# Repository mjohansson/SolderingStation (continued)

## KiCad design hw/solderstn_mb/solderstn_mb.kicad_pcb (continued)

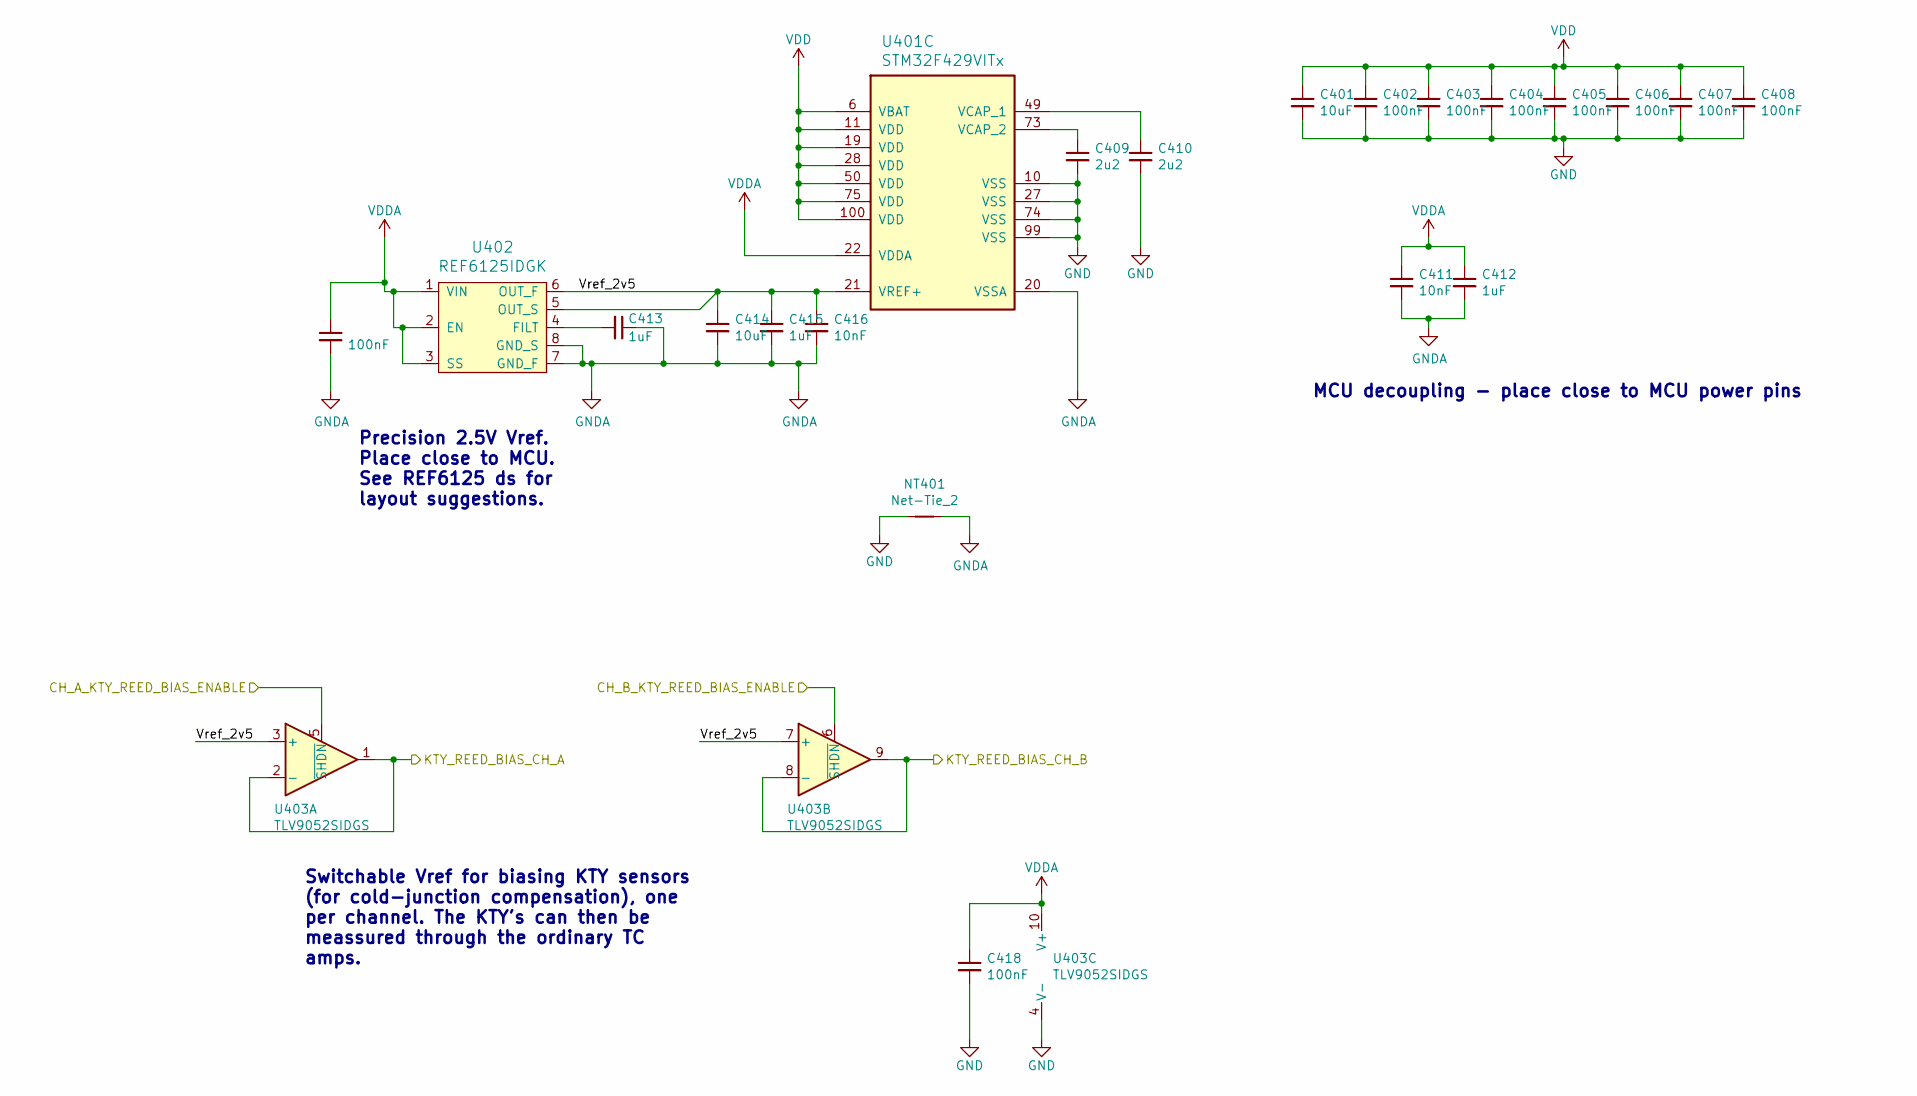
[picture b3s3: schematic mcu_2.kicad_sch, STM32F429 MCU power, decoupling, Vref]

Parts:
C401, C414: 10uF; C_0402_1005Metric; JLC_part Basic
C402, C403, C404, C405, C406, C407, C408, C417, C418: 100nF; C_0402_1005Metric; JLC_part Basic
C409, C410: 2u2; C_0603_1608Metric; JLC_part Basic
C411, C416: 10nF; C_0402_1005Metric; JLC_part Basic
C412, C413, C415: 1uF; C_0402_1005Metric; JLC_part Basic
NT401: Net-Tie_2; NetTie-2_SMD_Pad2.0mm
U401: STM32F429VITx; LQFP-100_14x14mm_P0.5mm; JLC_part Extended
U402: REF6125IDGK; VSSOP-8_3.0x3.0mm_P0.65mm
U403: TLV9052SIDGS; VSSOP-10_3x3mm_P0.5mm

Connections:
/STM32F429 MCU/CH_A_KTY_REED_BIAS_EN: U403.5 (~SHDN); also elsewhere on the board
/STM32F429 MCU/CH_B_KTY_REED_BIAS_EN: U403.6 (~SHDN); also elsewhere on the board
/STM32F429 PWR/KTY_REED_BIAS_CH_A: U403.1, U403.2 (-); also elsewhere on the board
/STM32F429 PWR/KTY_REED_BIAS_CH_B: U403.8 (-), U403.9; also elsewhere on the board
/STM32F429 PWR/Vref_2v5: C414.1, C415.1, C416.1, U401.21 (VREF+), U402.5 (OUT_S), U402.6 (OUT_F), U403.3 (+), U403.7 (+)
AGND: C401.2, C402.2, C403.2, C404.2, C405.2, C406.2, C407.2, C408.2, C409.2, C410.2, C411.2, C412.2, C413.1, C414.2, C415.2, C416.2, C417.2, C418.2, NT401.1, NT401.2, U401.10 (VSS), U401.20 (VSSA), U401.27 (VSS), U401.74 (VSS), U401.99 (VSS), U402.7 (GND_F), U402.8 (GND_S), U403.4 (V-); also elsewhere on the board
AVDD: C411.1, C412.1, C417.1, C418.1, U401.22 (VDDA), U402.1 (VIN), U402.2 (EN), U402.3 (SS), U403.10 (V+); also elsewhere on the board
unnamed: C409.1, U401.73 (VCAP_2)
unnamed: C410.1, U401.49 (VCAP_1)
unnamed: C413.2, U402.4 (FILT)
VCC: C401.1, C402.1, C403.1, C404.1, C405.1, C406.1, C407.1, C408.1, U401.6 (VBAT), U401.11 (VDD), U401.19 (VDD), U401.28 (VDD), U401.50 (VDD), U401.75 (VDD), U401.100 (VDD); also elsewhere on the board

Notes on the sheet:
MCU decoupling - place close to MCU power pins
Precision 2.5V Vref. Place close to MCU. See REF6125 ds for layout suggestions.
Switchable Vref for biasing KTY sensors (for cold-junction compensation), one per channel. The KTY's can then be meassured through the ordinary TC amps.

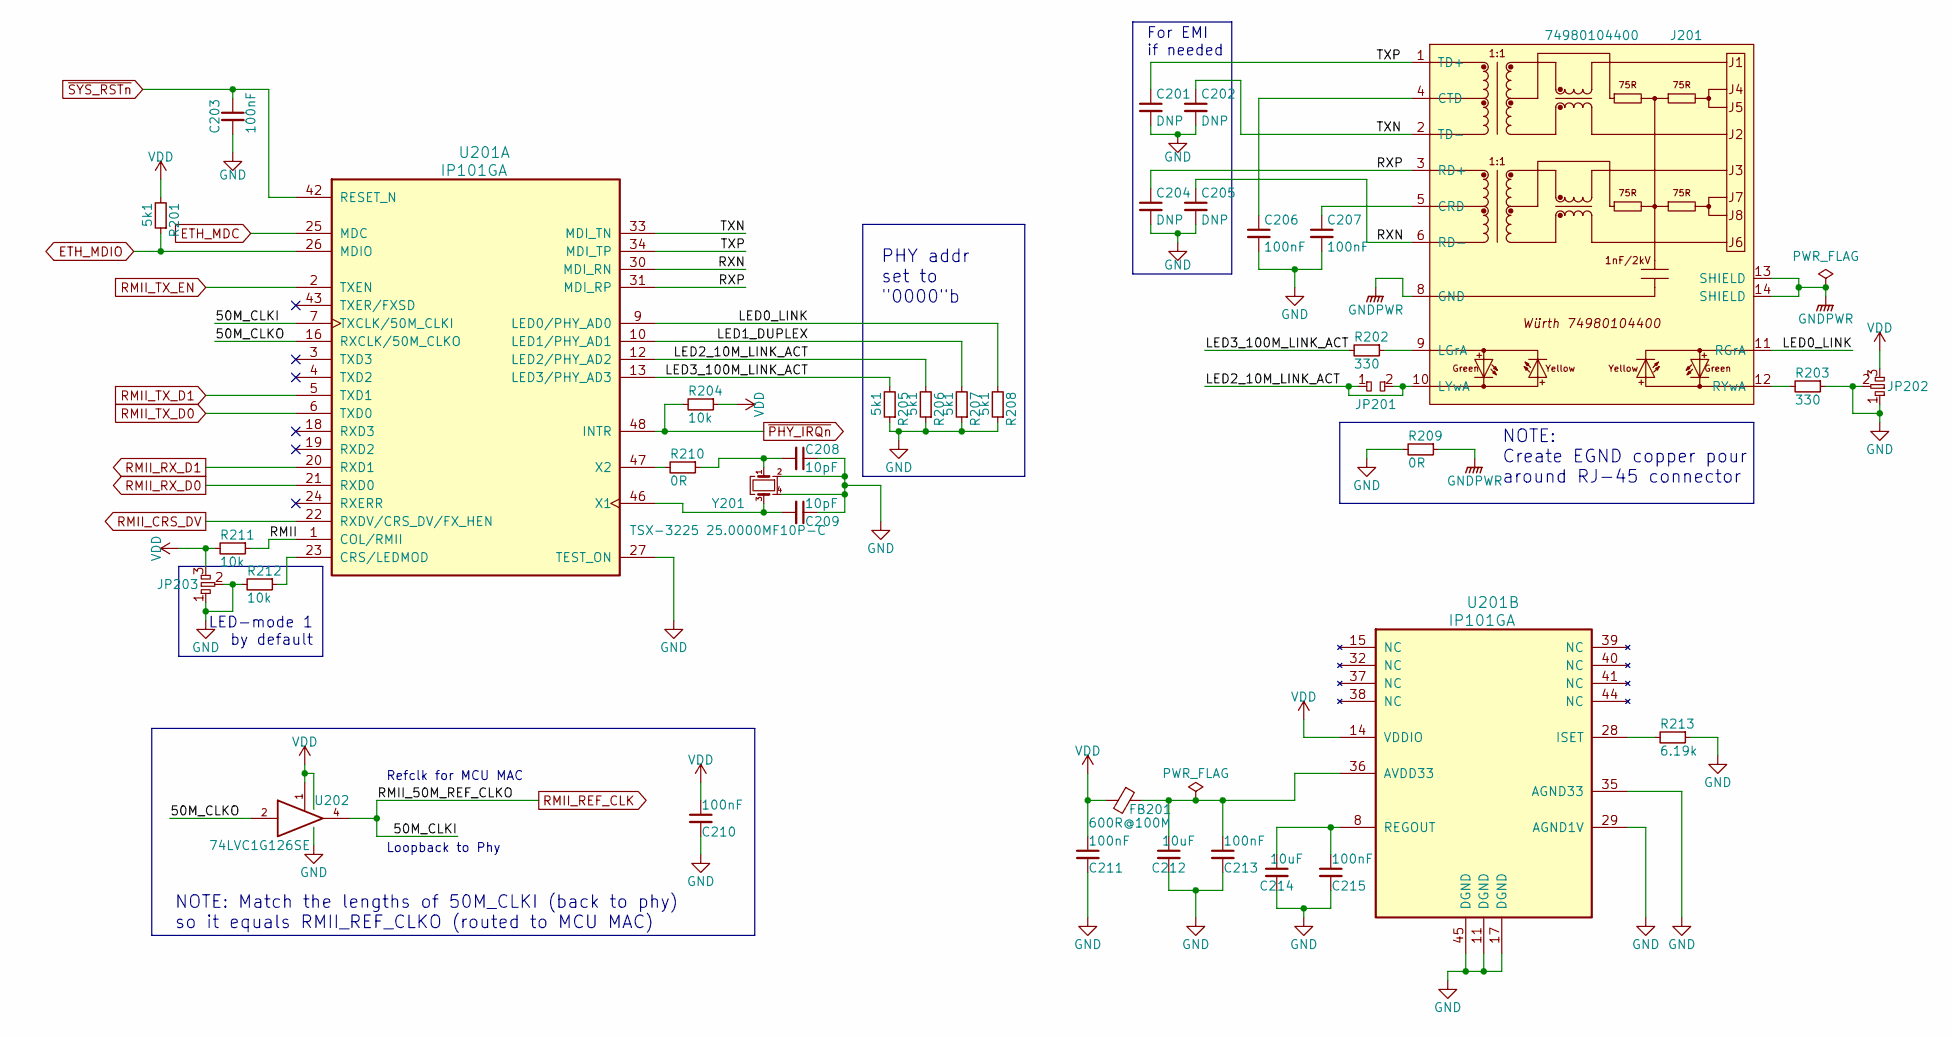
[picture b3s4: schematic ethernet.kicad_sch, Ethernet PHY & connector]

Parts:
C201, C202, C204, C205: DNP; C_0402_1005Metric; JLC_part Basic
C203, C206, C207, C210, C211, C213, C215: 100nF; C_0402_1005Metric; JLC_part Basic
C208, C209: 10pF; C_0402_1005Metric; JLC_part Basic
C212, C214: 10uF; C_0402_1005Metric; JLC_part Basic
FB201: 600R@100M; L_0603_1608Metric; JLC_part Basic
J201: 74980104400; 74980104400_WE-RJ45_LAN_trx
JP201: dogbone_2_ud; db2_ud_0402
JP202, JP203: dogbone_3_ud; db3_ud_0402
R201, R205, R206, R207, R208: 5k1; R_0402_1005Metric; JLC_part Basic
R202, R203: 330; R_0402_1005Metric; JLC_part Basic
R204, R211, R212: 10k; R_0402_1005Metric; JLC_part Basic
R209, R210: 0R; R_0402_1005Metric; JLC_part Basic
R213: 6.19k; R_0402_1005Metric; JLC_part Extended
U201: IP101GA; LQFP-48_7x7mm_P0.5mm; JLC_part Extended
U202: 74LVC1G126SE; SOT-353_SC-70-5_Handsoldering; JLC_part Extended
Y201: TSX-3225 25.0000MF10P-C; Crystal_SMD_SeikoEpson_TSX3225-4Pin_3.2x2.5mm; JLC_part Basic

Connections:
/Ethernet/50M_CLKO: U201.16 (RXCLK/50M_CLKO), U202.2
/Ethernet/LED0_LINK: J201.11 (RGrA), R208.2, U201.9 (LED0/PHY_AD0)
/Ethernet/LED1_DUPLEX: R207.2, U201.10 (LED1/PHY_AD1)
/Ethernet/LED2_10M_LINK_ACT: J201.10 (LYwA), JP201.1, JP201.2, R206.2, U201.12 (LED2/PHY_AD2)
/Ethernet/LED3_100M_LINK_ACT: R202.2, R205.2, U201.13 (LED3/PHY_AD3)
/Ethernet/RMII: R211.1, U201.1 (COL/RMII)
/Ethernet/RXN: C205.1, J201.6 (RD-), U201.30 (MDI_RN)
/Ethernet/RXP: C204.1, J201.3 (RD+), U201.31 (MDI_RP)
/Ethernet/TXN: C202.1, J201.2 (TD-), U201.33 (MDI_TN)
/Ethernet/TXP: C201.1, J201.1 (TD+), U201.34 (MDI_TP)
AGND: C201.2, C202.2, C203.2, C204.2, C205.2, C206.2, C207.2, C208.1, C209.1, C210.2, C211.2, C212.2, C213.2, C214.2, C215.2, JP202.1, JP202.2, JP203.1, JP203.2, R203.1, R205.1, R206.1, R207.1, R208.1, R209.2, R212.2, R213.1, U201.11 (DGND), U201.17 (DGND), U201.27 (TEST_ON), U201.29 (AGND1V), U201.35 (AGND33), U201.45 (DGND), U202.3 (GND), Y201.2, Y201.4; also elsewhere on the board
ETH_MDC: U201.25 (MDC); also elsewhere on the board
ETH_MDIO: R201.1, U201.26 (MDIO); also elsewhere on the board
GNDPWR: J201.8 (GND), J201.13 (SHIELD), J201.14 (SHIELD), R209.1
unnamed: C206.1, J201.4 (CTD)
unnamed: C207.1, J201.5 (CRD)
unnamed: C208.2, R210.1, Y201.1
unnamed: C209.2, U201.46 (X1), Y201.3
unnamed: C212.1, C213.1, FB201.1, U201.36 (AVDD33)
unnamed: C214.1, C215.1, U201.8 (REGOUT)
unnamed: J201.9 (LGrA), R202.1
unnamed: J201.12 (RYwA), R203.2
unnamed: R210.2, U201.47 (X2)
unnamed: R212.1, U201.23 (CRS/LEDMOD)
unnamed: R213.2, U201.28 (ISET)
RMII_CRS_DV: U201.22 (RXDV/CRS_DV/FX_HEN); also elsewhere on the board
RMII_REF_CLK: U201.7 (TXCLK/50M_CLKI), U202.4; also elsewhere on the board
RMII_RX_D0: U201.21 (RXD0); also elsewhere on the board
RMII_RX_D1: U201.20 (RXD1); also elsewhere on the board
RMII_TX_D0: U201.6 (TXD0); also elsewhere on the board
RMII_TX_D1: U201.5 (TXD1); also elsewhere on the board
RMII_TX_EN: U201.2 (TXEN); also elsewhere on the board
VCC: C210.1, C211.1, FB201.2, JP202.3, JP203.3, R201.2, R204.1, R211.2, U201.14 (VDDIO), U202.1, U202.5 (VCC); also elsewhere on the board
~PHY_IRQn: R204.2, U201.48 (INTR); also elsewhere on the board
~SYS_RSTn: C203.1, U201.42 (RESET_N); also elsewhere on the board

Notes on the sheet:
Refclk for MCU MAC
NOTE: Create EGND copper pour around RJ-45 connector
PHY addr set to "0000"b
Loopback to Phy
For EMI if needed
LED-mode 1 by default
NOTE: Match the lengths of 50M_CLKI (back to phy) so it equals RMII_REF_CLKO (routed to MCU MAC)

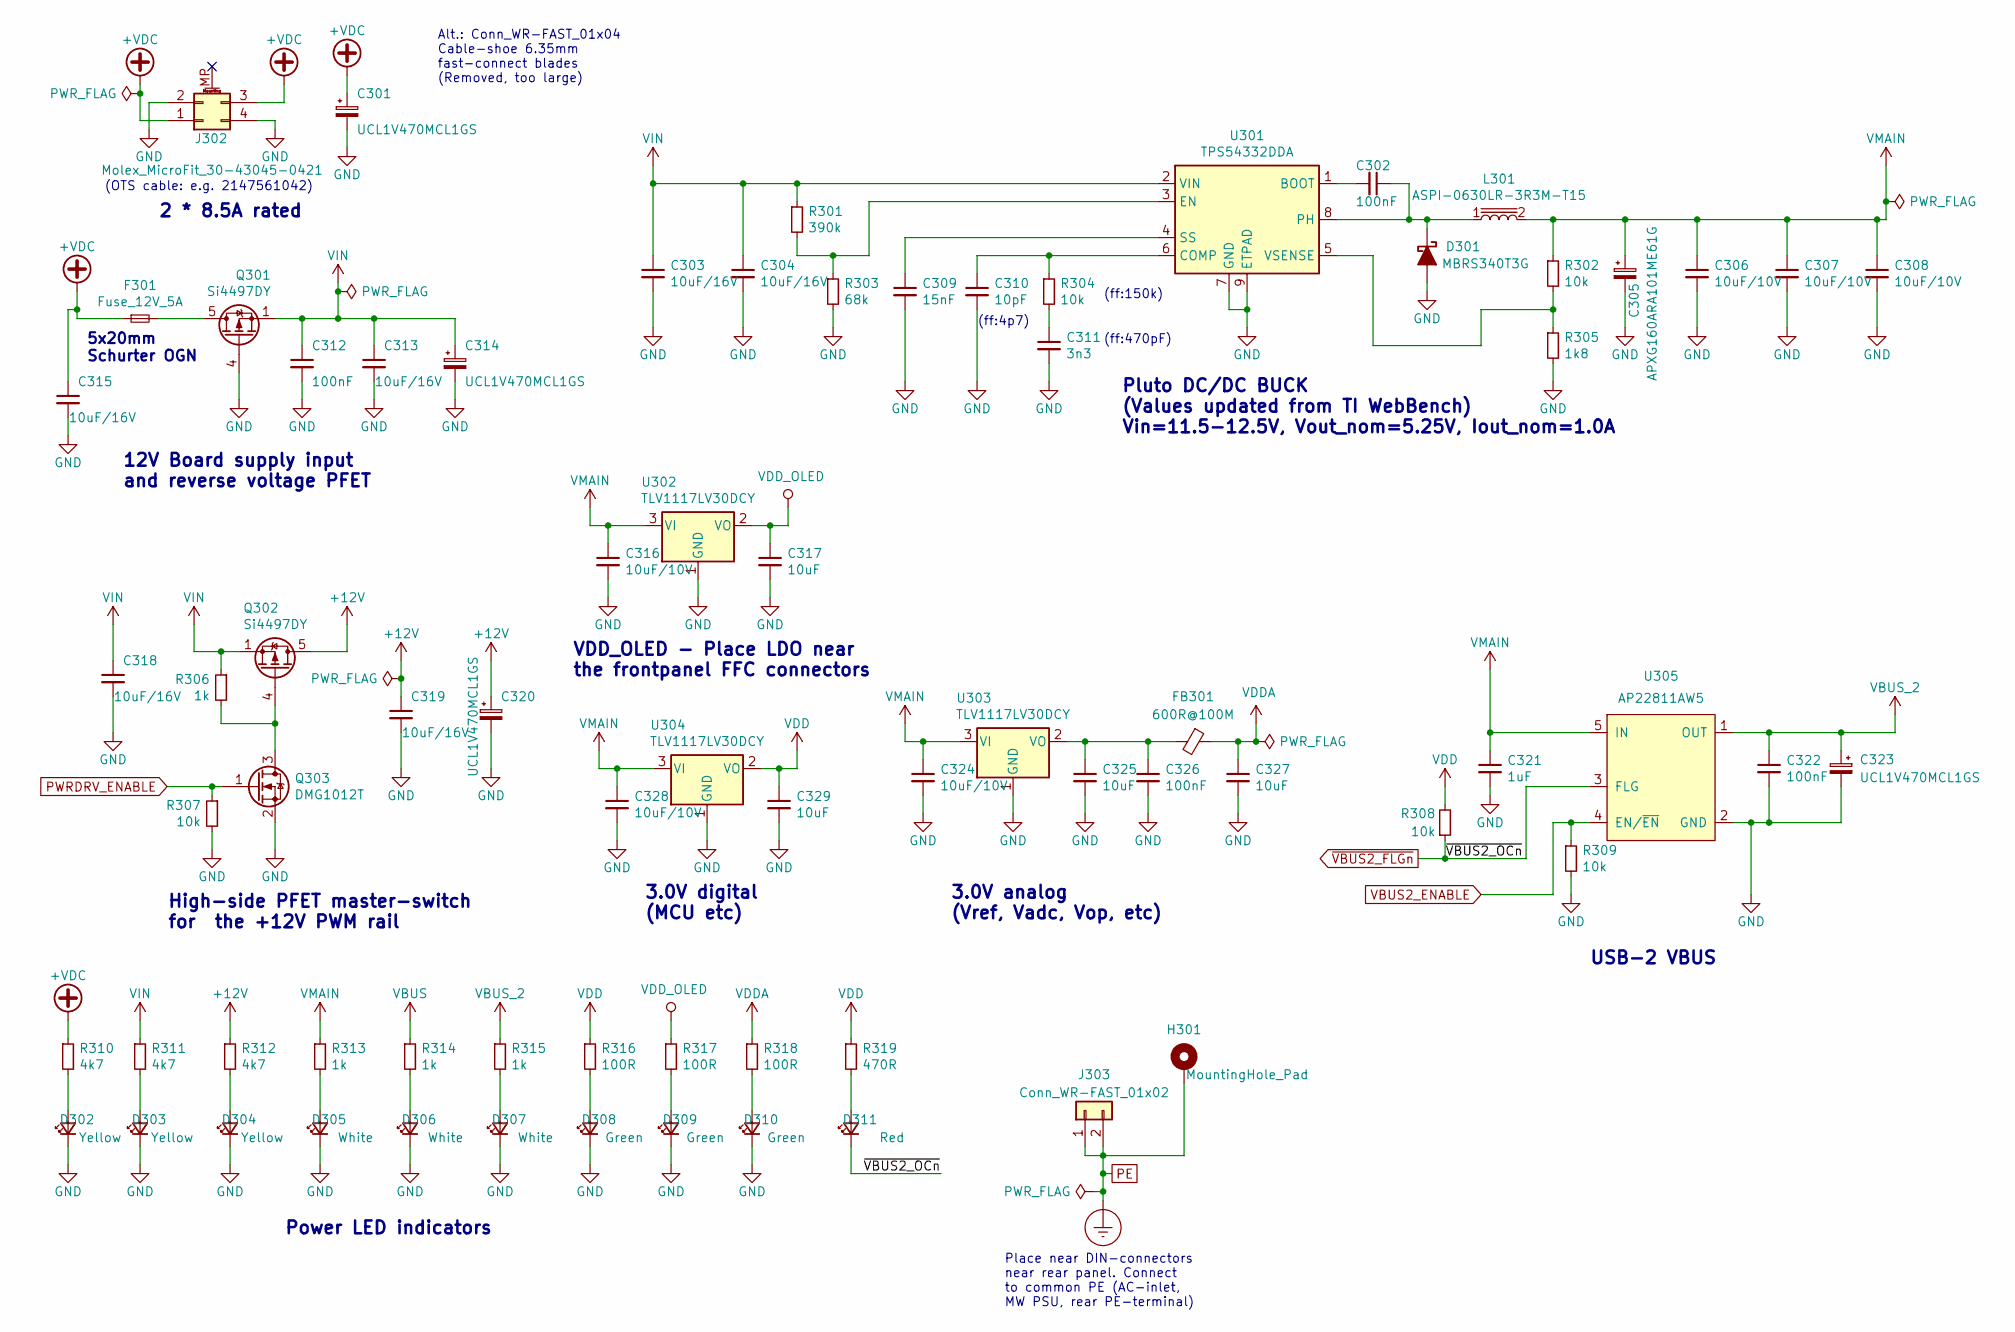
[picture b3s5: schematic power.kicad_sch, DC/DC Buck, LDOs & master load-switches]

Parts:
C301, C314, C320, C323: UCL1V470MCL1GS; CP_Elec_6.3x5.8
C302, C312, C322, C326: 100nF; C_0402_1005Metric; JLC_part Basic
C303, C304, C313, C315, C318, C319: 10uF/16V; C_0805_2012Metric; JLC_part Basic
C305: APXG160ARA101ME61G; CP_Elec_5x5.8
C306, C307, C308, C316, C324, C328: 10uF/10V; C_0603_1608Metric; JLC_part Basic
C309: 15nF; C_0603_1608Metric; JLC_part Basic
C310: 10pF; C_0402_1005Metric; JLC_part Basic
C311: 3n3; C_0402_1005Metric; JLC_part Basic
C317, C325, C327, C329: 10uF; C_0402_1005Metric; JLC_part Basic
C321: 1uF; C_0402_1005Metric; JLC_part Basic
D301: MBRS340T3G; MBRS3xx_SMC_CASE_403AC; JLC_part Extended
D302, D303, D304: Yellow; LED_0603_1608Metric; JLC_part Basic
D305, D306, D307: White; LED_0603_1608Metric; JLC_part Basic
D308, D309, D310: Green; LED_0603_1608Metric; JLC_part Basic
D311: Red; LED_0603_1608Metric; JLC_part Basic
F301: Fuse_12V_5A; Fuseholder_5x20mm_Schurter_OGN-0031.8201
FB301: 600R@100M; L_0603_1608Metric; JLC_part Basic
H301: MountingHole_Pad; MountingHole_3.5mm_Pad_Via
J302: Molex_MicroFit_30-43045-0421; Molex_Micro-Fit_3.0_43045-0421_2x02-1MP_P3.00mm_Horizontal
J303: Conn_WR-FAST_01x02; WR-FAST_508_2_V
L301: ASPI-0630LR-3R3M-T15; ASPI-0603LR
Q301, Q302: Si4497DY; SOIC-8_3.9x4.9mm_P1.27mm; JLC_part Extended
Q303: DMG1012T; SOT-523_handsoldering; JLC_part Extended
R301: 390k; R_0603_1608Metric; JLC_part Basic
R302, R304, R307, R308, R309: 10k; R_0402_1005Metric; JLC_part Basic
R303: 68k; R_0603_1608Metric; JLC_part Basic
R305: 1k8; R_0603_1608Metric; JLC_part Basic
R306, R313, R314, R315: 1k; R_0402_1005Metric; JLC_part Basic
R310, R311, R312: 4k7; R_0402_1005Metric; JLC_part Basic
R316, R317, R318: 100R; R_0402_1005Metric; JLC_part Basic
R319: 470R; R_0402_1005Metric; JLC_part Basic
U301: TPS54332DDA; TI_SO-PowerPAD-8_ThermalVias; JLC_part Extended
U302, U303, U304: TLV1117LV30DCY; SOT-223-3_TabPin2
U305: AP22811AW5; TSOT-23-5

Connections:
+12V: C319.1, C320.1, Q302.5 (D), Q302.6 (D), Q302.7 (D), Q302.8 (D), R312.1; also elsewhere on the board
+VDC: C301.1, C315.1, F301.1, J302.1, J302.3, R310.1
AGND: C301.2, C303.2, C304.2, C305.2, C306.2, C307.2, C308.2, C309.2, C310.2, C311.2, C312.2, C313.2, C314.2, C315.2, C316.2, C317.2, C318.2, C319.2, C320.2, C321.2, C322.2, C323.2, C324.2, C325.2, C326.2, C327.2, C328.2, C329.2, D301.2 (A), D302.1 (K), D303.1 (K), D304.1 (K), D305.1 (K), D306.1 (K), D307.1 (K), D308.1 (K), D309.1 (K), D310.1 (K), J302.2, J302.4, Q301.4 (G), Q303.2 (S), R303.2, R305.2, R307.2, R309.2, U301.7 (GND), U301.9 (ETPAD), U302.1 (GND), U303.1 (GND), U304.1 (GND), U305.2 (GND); also elsewhere on the board
AVDD: C327.1, FB301.1, R318.1; also elsewhere on the board
unnamed: C302.1, D301.1 (K), L301.1, U301.8 (PH)
unnamed: C302.2, U301.1 (BOOT)
unnamed: C309.1, U301.4 (SS)
unnamed: C310.1, R304.1, U301.6 (COMP)
unnamed: C311.1, R304.2
unnamed: C325.1, C326.1, FB301.2, U303.2 (VO)
unnamed: D302.2 (A), R310.2
unnamed: D303.2 (A), R311.2
unnamed: D304.2 (A), R312.2
unnamed: D305.2 (A), R313.2
unnamed: D306.2 (A), R314.2
unnamed: D307.2 (A), R315.2
unnamed: D308.2 (A), R316.2
unnamed: D309.2 (A), R317.2
unnamed: D310.2 (A), R318.2
unnamed: D311.2 (A), R319.2
unnamed: F301.2, Q301.5 (D), Q301.6 (D), Q301.7 (D), Q301.8 (D)
unnamed: Q302.4 (G), Q303.3 (D), R306.2
unnamed: R301.2, R303.1, U301.3 (EN)
unnamed: R302.2, R305.1, U301.5 (VSENSE)
PE: H301.1, J303.1, J303.2; also elsewhere on the board
PWRDRV_ENABLE: Q303.1 (G), R307.1; also elsewhere on the board
VBUS: R314.1; also elsewhere on the board
VBUS2_ENABLE: R309.1, U305.4 (EN/~EN); also elsewhere on the board
VBUS_2: C322.1, C323.1, R315.1, U305.1 (OUT); also elsewhere on the board
VCC: C329.1, R308.2, R316.1, R319.1, U304.2 (VO); also elsewhere on the board
VDD_OLED: C317.1, R317.1, U302.2 (VO); also elsewhere on the board
VIN: C303.1, C304.1, C312.1, C313.1, C314.1, C318.1, Q301.1 (S), Q301.2 (S), Q301.3 (S), Q302.1 (S), Q302.2 (S), Q302.3 (S), R301.1, R306.1, R311.1, U301.2 (VIN); also elsewhere on the board
VMAIN: C305.1, C306.1, C307.1, C308.1, C316.1, C321.1, C324.1, C328.1, L301.2, R302.1, R313.1, U302.3 (VI), U303.3 (VI), U304.3 (VI), U305.5 (IN); also elsewhere on the board
~VBUS2_FLGn: D311.1 (K), R308.1, U305.3 (FLG); also elsewhere on the board

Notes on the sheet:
USB-2 VBUS
High-side PFET master-switch for the +12V PWM rail
Power LED indicators
2 * 8.5A rated
Alt.: Conn_WR-FAST_01x04 Cable-shoe 6.35mm fast-connect blades (Removed, too large)
3.0V analog (Vref, Vadc, Vop, etc)
(ff:150k)
12V Board supply input and reverse voltage PFET
(ff:470pF)
(ff:4p7)
(OTS cable: e.g. 2147561042)
5x20mm Schurter OGN
Place near DIN-connectors near rear panel. Connect to common PE (AC-inlet, MW PSU, rear PE-terminal)
VDD_OLED - Place LDO near the frontpanel FFC connectors
Pluto DC/DC BUCK (Values updated from TI WebBench) Vin=11.5-12.5V, Vout_nom=5.25V, Iout_nom=1.0A
3.0V digital (MCU etc)

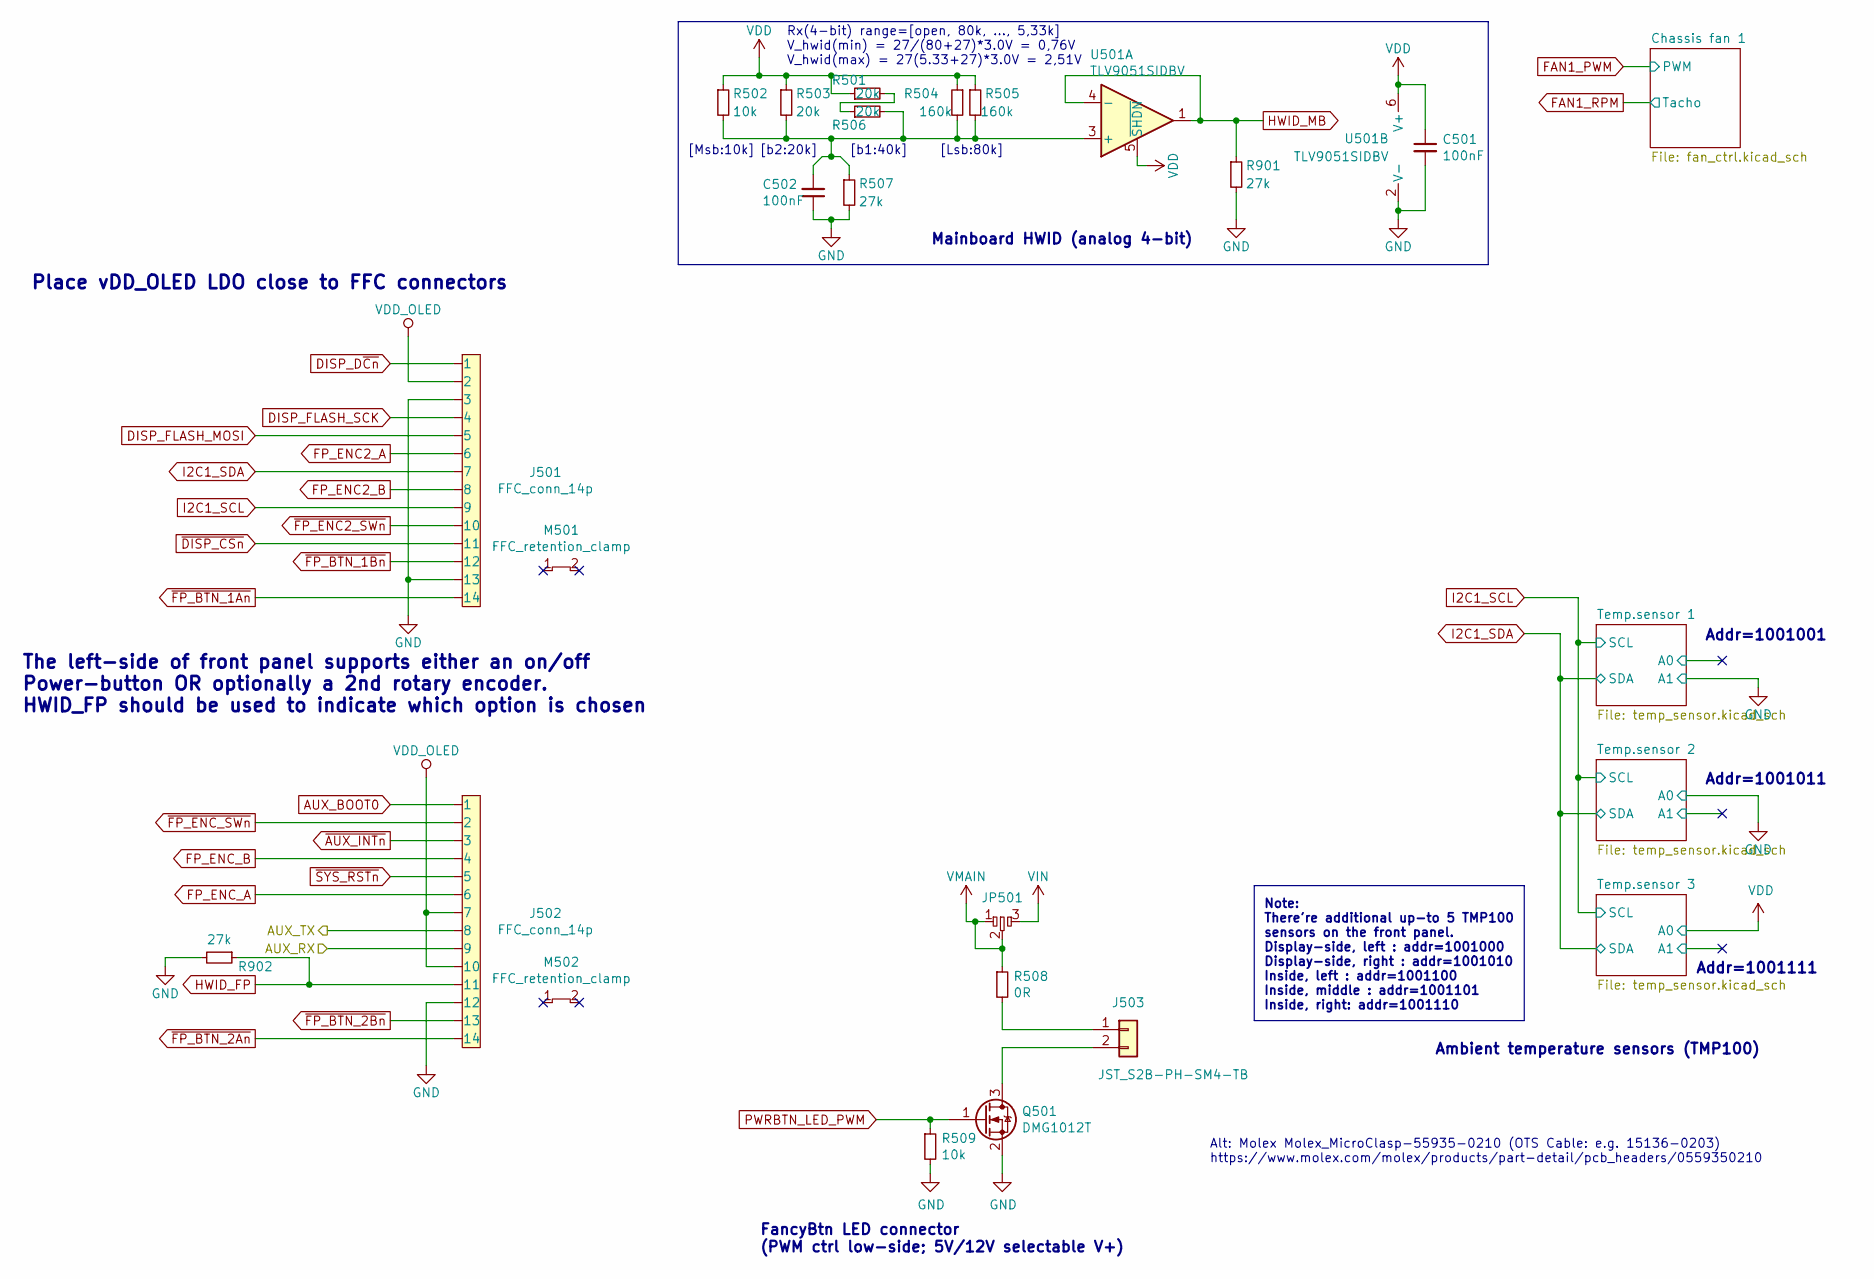
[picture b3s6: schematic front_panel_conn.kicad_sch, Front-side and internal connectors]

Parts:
C501, C502: 100nF; C_0402_1005Metric; JLC_part Basic
J501, J502: FFC_conn_14p; FPC_14p_05mm-Molex_5052781433
J503: JST_S2B-PH-SM4-TB; JST_PH_S2B-PH-SM4-TB_1x02-1MP_P2.00mm_Horizontal
JP501: dogbone_3_ud; db3_ud_0402
M501, M502: FFC_retention_clamp; FFC_retention_clamp_14pin_7_5mm
Q501: DMG1012T; SOT-523_handsoldering; JLC_part Extended
R501, R503, R506: 20k; R_0402_1005Metric; JLC_part Basic
R502, R509: 10k; R_0402_1005Metric; JLC_part Basic
R504, R505: 160k; R_0603_1608Metric; JLC_part Basic
R507, R901, R902: 27k; R_0402_1005Metric; JLC_part Basic
R508: 0R; R_0402_1005Metric; JLC_part Basic
U501: TLV9051SIDBV; TSOT-23-6

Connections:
/Front panel connections/AUX_RX: J502.9; also elsewhere on the board
/Front panel connections/AUX_TX: J502.8; also elsewhere on the board
AGND: C501.2, C502.1, J501.3, J501.13, J502.12, Q501.2 (S), R507.2, R509.2, R901.2, R902.2, U501.2 (V-); also elsewhere on the board
AUX_BOOT0: J502.1; also elsewhere on the board
DISP_D~Cn: J501.1; also elsewhere on the board
DISP_FLASH_MOSI: J501.5; also elsewhere on the board
DISP_FLASH_SCK: J501.4; also elsewhere on the board
FP_ENC2_A: J501.6; also elsewhere on the board
FP_ENC2_B: J501.8; also elsewhere on the board
FP_ENC_A: J502.6; also elsewhere on the board
FP_ENC_B: J502.4; also elsewhere on the board
HWID_FP: J502.11, R902.1; also elsewhere on the board
HWID_MB: R901.1, U501.1, U501.4 (-); also elsewhere on the board
I2C1_SCL: J501.9; also elsewhere on the board
I2C1_SDA: J501.7; also elsewhere on the board
unnamed: C502.2, R502.2, R503.2, R504.2, R505.2, R506.2, R507.1, U501.3 (+)
unnamed: J503.1, R508.2
unnamed: J503.2, Q501.3 (D)
unnamed: R501.2, R506.1
PWRBTN_LED_PWM: Q501.1 (G), R509.1; also elsewhere on the board
VCC: C501.1, R501.1, R502.1, R503.1, R504.1, R505.1, U501.5 (~SHDN), U501.6 (V+); also elsewhere on the board
VDD_OLED: J501.2, J502.7, J502.10; also elsewhere on the board
VIN: JP501.3; also elsewhere on the board
VMAIN: JP501.1, JP501.2, R508.1; also elsewhere on the board
~AUX_INTn: J502.3; also elsewhere on the board
~DISP_CSn: J501.11; also elsewhere on the board
~FP_BTN_1An: J501.14; also elsewhere on the board
~FP_BTN_1Bn: J501.12; also elsewhere on the board
~FP_BTN_2An: J502.14; also elsewhere on the board
~FP_BTN_2Bn: J502.13; also elsewhere on the board
~FP_ENC2_SWn: J501.10; also elsewhere on the board
~FP_ENC_SWn: J502.2; also elsewhere on the board
~SYS_RSTn: J502.5; also elsewhere on the board

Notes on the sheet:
Addr=1001011
Alt: Molex Molex_MicroClasp-55935-0210 (OTS Cable: e.g. 15136-0203) https://www.molex.com/molex/products/part-detail/pcb_headers/0559350210
Rx(4-bit) range=[open, 80k, ..., 5,33k] V_hwid(min) = 27/(80+27)*3.0V = 0,76V V_hwid(max) = 27(5.33+27)*3.0V = 2,51V
[b2:20k]
[Lsb:80k]
Addr=1001001
Note: There're additional up-to 5 TMP100 sensors on the front panel. Display-side, left : addr=1001000 Display-side, right : addr=1001010 Inside, left : addr=1001100 Inside, middle : addr=1001101 Inside, right: addr=1001110
The left-side of front panel supports either an on/off Power-button OR optionally a 2nd rotary encoder. HWID_FP should be used to indicate which option is chosen
Ambient temperature sensors (TMP100)
Place vDD_OLED LDO close to FFC connectors
Addr=1001111
FancyBtn LED connector (PWM ctrl low-side; 5V/12V selectable V+)
Mainboard HWID (analog 4-bit)
[Msb:10k]
[b1:40k]

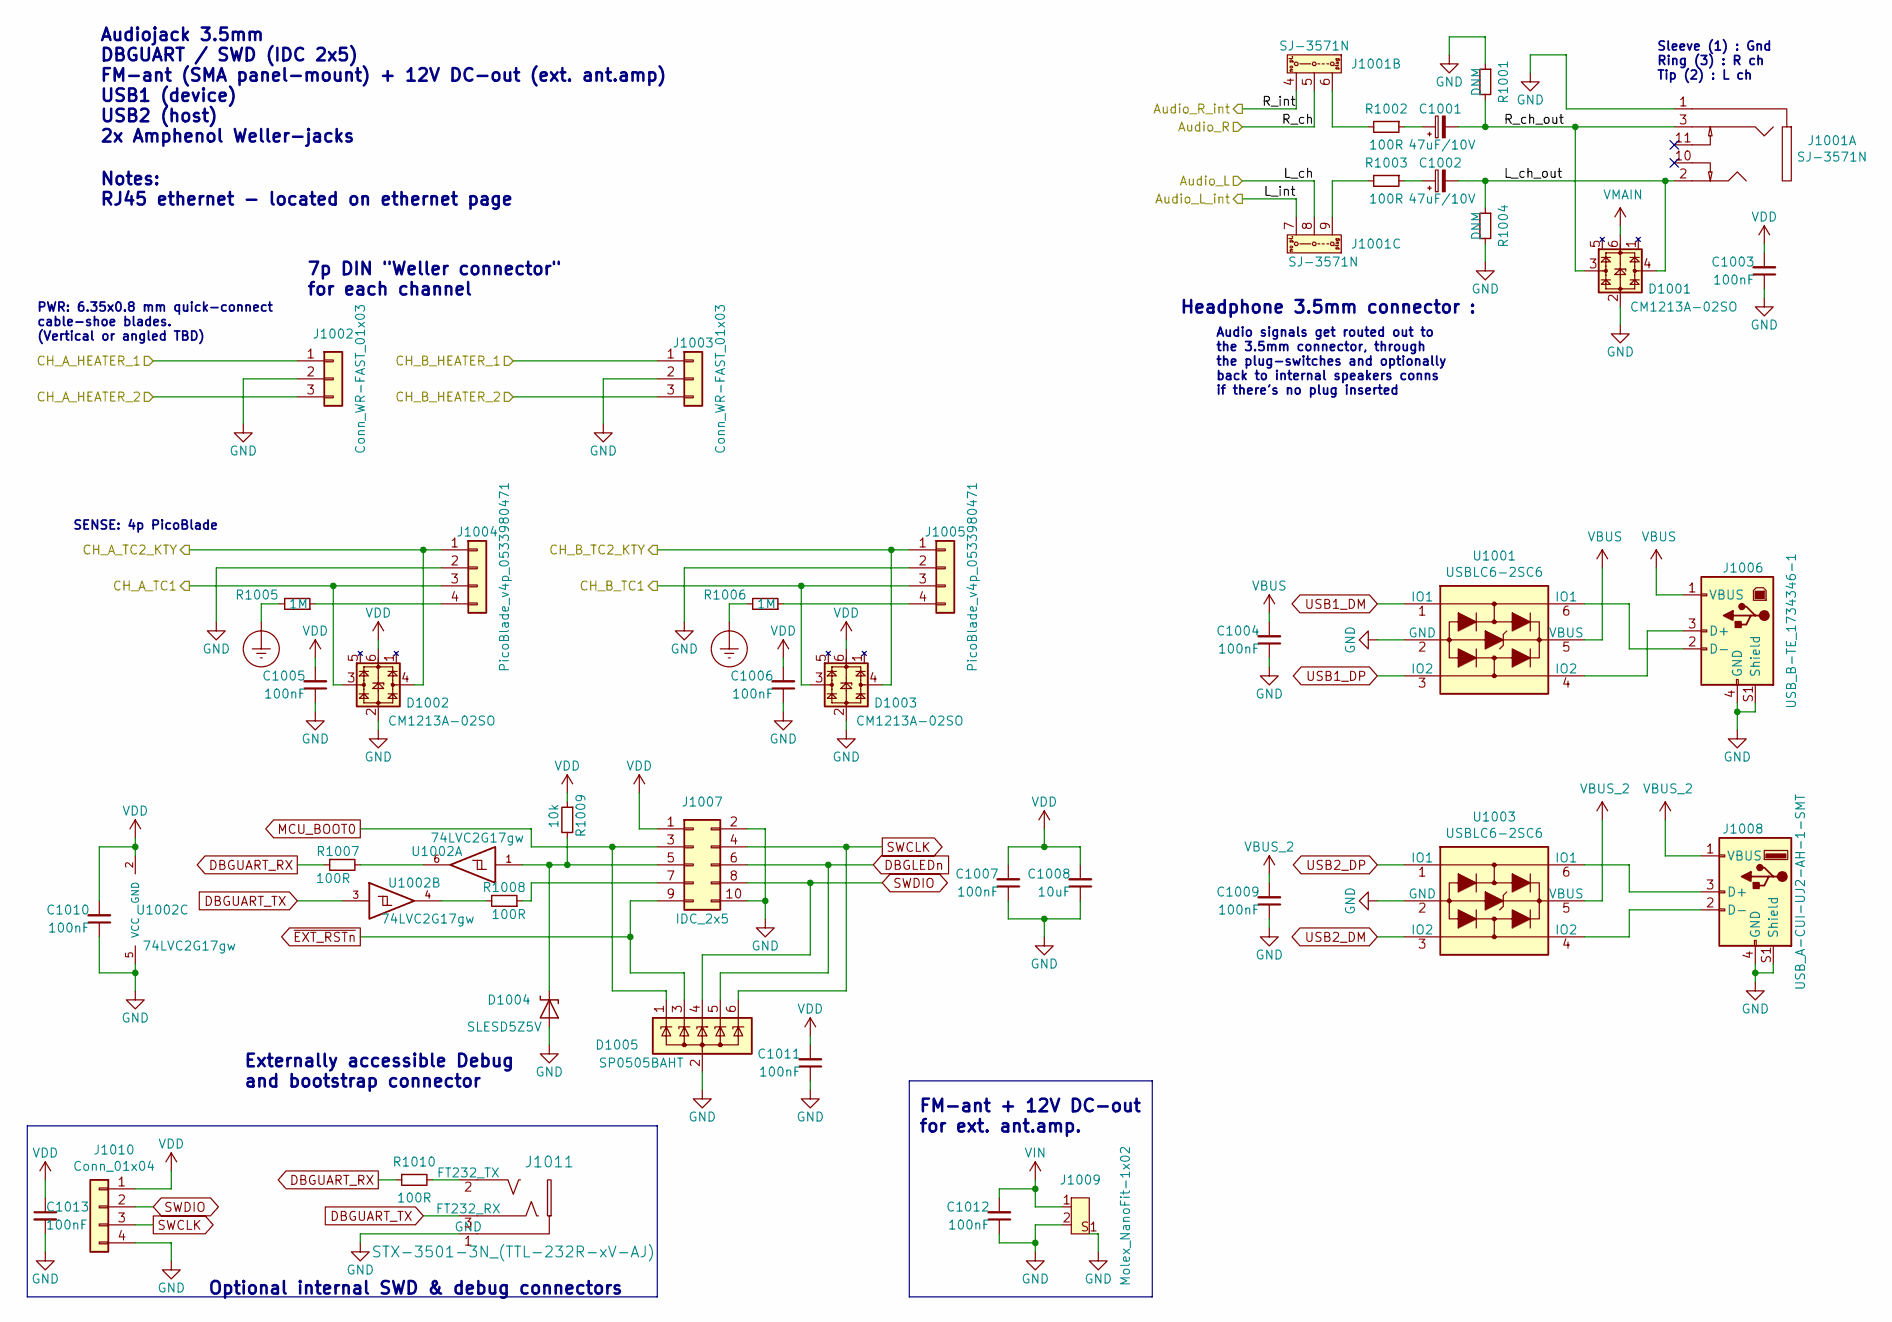
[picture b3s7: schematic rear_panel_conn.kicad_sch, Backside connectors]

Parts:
C1001, C1002: 47uF/10V; CP_Elec_6.3x5.8
C1003, C1004, C1005, C1006, C1007, C1009, C1010, C1011, C1012, C1013: 100nF; C_0402_1005Metric; JLC_part Basic
C1008: 10uF; C_0402_1005Metric; JLC_part Basic
D1001, D1002, D1003: CM1213A-02SO; SC-74-6
D1004: SLESD5Z5V; D_SOD-523
D1005: SP0505BAHT; TSOT-23-6
J1001: SJ-3571N
J1002, J1003: Conn_WR-FAST_01x03; WR-FAST_508_3_V
J1004, J1005: PicoBlade_v4p_0533980471; Molex_PicoBlade_53398-0471_1x04-1MP_P1.25mm_Vertical
J1006: USB_B-TE_1734346-1; TE_1734346
J1007: IDC_2x5; IDC-Header_2x05_P2.54mm_Horizontal
J1008: USB_A-CUI-UJ2-AH-1-SMT; CUI-UJ2_AH_1_SMT
J1009: Molex_NanoFit-1x02; Molex_NanoFit_105430-1102_1x02_P2.50mm_Horizontal
J1010: Conn_01x04; PinHeader_1x04_P2.54mm_Vertical
J1011: STX-3501-3N_(TTL-232R-xV-AJ); STX3501_smd
R1001, R1004: DNM; R_0402_1005Metric
R1002, R1003, R1007, R1008, R1010: 100R; R_0402_1005Metric; JLC_part Basic
R1005, R1006: 1M; R_0402_1005Metric; JLC_part Basic
R1009: 10k; R_0402_1005Metric; JLC_part Basic
U1001, U1003: USBLC6-2SC6; TSOT-23-6; JLC_part Extended
U1002: 74LVC2G17gw; SOT-363_SC-70-6_Handsoldering; JLC_part Extended

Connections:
/Rear panel connections/CH_A_TC1: D1002.3 (CH1), J1004.3; also elsewhere on the board
/Rear panel connections/CH_B_TC1: D1003.3 (CH1), J1005.3; also elsewhere on the board
/Rear panel connections/L_ch: J1001.8 (b); also elsewhere on the board
/Rear panel connections/L_ch_out: C1002.2, D1001.4 (CH2), J1001.2 (tip), R1004.1
/Rear panel connections/L_int: J1001.7 (nc_b); also elsewhere on the board
/Rear panel connections/R_ch: J1001.5 (a); also elsewhere on the board
/Rear panel connections/R_ch_out: C1001.2, D1001.3 (CH1), J1001.3 (ring), R1001.2
/Rear panel connections/R_int: J1001.4 (nc_a); also elsewhere on the board
/Weller contol/CH_A_KTY_SNS: D1002.4 (CH2), J1004.1; also elsewhere on the board
/Weller contol/CH_B_KTY_SNS: D1003.4 (CH2), J1005.1; also elsewhere on the board
/Weller contol/Channel A/HEATER_1: J1002.1; also elsewhere on the board
/Weller contol/Channel A/HEATER_2: J1002.3; also elsewhere on the board
/Weller contol/Channel B/HEATER_1: J1003.1; also elsewhere on the board
/Weller contol/Channel B/HEATER_2: J1003.3; also elsewhere on the board
AGND: C1003.1, C1004.1, C1005.1, C1006.1, C1007.1, C1008.1, C1009.1, C1010.1, C1011.1, C1012.1, C1013.2, D1001.2 (VN), D1002.2 (VN), D1003.2 (VN), D1004.2 (A), D1005.2 (A), J1001.1 (sleeve), J1002.2, J1003.2, J1004.2, J1005.2, J1006.4 (GND), J1006.S1 (Shield), J1006.S2 (Shield), J1007.2, J1007.10, J1008.4 (GND), J1008.S1 (Shield), J1008.S2 (Shield), J1009.2, J1009.S1, J1009.S2, J1010.4, J1011.1 (GND), R1001.1, R1004.2, U1001.2 (GND), U1002.5 (VCC), U1003.2 (GND); also elsewhere on the board
DBGLEDn: D1005.5 (K), J1007.6; also elsewhere on the board
DBGUART_RX: R1007.1, R1010.1; also elsewhere on the board
DBGUART_TX: J1011.3 (FT232_RX), U1002.3; also elsewhere on the board
MCU_BOOT0: D1005.1 (K), J1007.3; also elsewhere on the board
unnamed: C1001.1, R1002.1
unnamed: C1002.1, R1003.1
unnamed: D1004.1 (C), J1007.5, R1009.2, U1002.1
unnamed: J1001.6 (no_a), R1002.2
unnamed: J1001.9 (no_b), R1003.2
unnamed: J1004.4, R1005.1
unnamed: J1005.4, R1006.1
unnamed: J1006.2 (D-), U1001.6 (IO1)
unnamed: J1006.3 (D+), U1001.4 (IO2)
unnamed: J1007.7, R1008.1
unnamed: J1008.2 (D-), U1003.4 (IO2)
unnamed: J1008.3 (D+), U1003.6 (IO1)
unnamed: J1011.2 (FT232_TX), R1010.2
unnamed: R1007.2, U1002.6
unnamed: R1008.2, U1002.4
PE: R1005.2, R1006.2; also elsewhere on the board
SWCLK: D1005.6 (K), J1007.4, J1010.3; also elsewhere on the board
SWDIO: D1005.4 (K), J1007.8, J1010.2; also elsewhere on the board
USB1_DM: U1001.1 (IO1); also elsewhere on the board
USB1_DP: U1001.3 (IO2); also elsewhere on the board
USB2_DM: U1003.3 (IO2); also elsewhere on the board
USB2_DP: U1003.1 (IO1); also elsewhere on the board
VBUS: C1004.2, J1006.1 (VBUS), U1001.5 (VBUS); also elsewhere on the board
VBUS_2: C1009.2, J1008.1 (VBUS), U1003.5 (VBUS); also elsewhere on the board
VCC: C1003.2, C1005.2, C1006.2, C1007.2, C1008.2, C1010.2, C1011.2, C1013.1, D1002.6 (VP), D1003.6 (VP), J1007.1, J1010.1, R1009.1, U1002.2 (GND); also elsewhere on the board
VIN: C1012.2, J1009.1; also elsewhere on the board
VMAIN: D1001.6 (VP); also elsewhere on the board
~EXT_RSTn: D1005.3 (K), J1007.9; also elsewhere on the board

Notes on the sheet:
PWR: 6.35x0.8 mm quick-connect cable-shoe blades. (Vertical or angled TBD)
FM-ant + 12V DC-out for ext. ant.amp.
Sleeve (1) : Gnd Ring (3) : R ch Tip (2) : L ch
SENSE: 4p PicoBlade
Optional internal SWD & debug connectors
Headphone 3.5mm connector :
Audio signals get routed out to the 3.5mm connector, through the plug-switches and optionally back to internal speakers conns if there's no plug inserted
7p DIN "Weller connector" for each channel
Notes: RJ45 ethernet - located on ethernet page
Audiojack 3.5mm DBGUART / SWD (IDC 2x5) FM-ant (SMA panel-mount) + 12V DC-out (ext. ant.amp) USB1 (device) USB2 (host) 2x Amphenol Weller-jacks
Externally accessible Debug and bootstrap connector
